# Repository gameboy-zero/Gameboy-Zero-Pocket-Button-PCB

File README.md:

&emsp;&emsp;&emsp;&emsp;&emsp;&emsp;&emsp;&emsp;&emsp;&emsp;&emsp;
# Informations
This button PCB is for the Gameboy Pocket to make a Gameboy Zero or an Arduboy.

## Pictures of the PCB

You find pictures in the images folder.

## Contributors:
DerNuntius

## Contact me
If you have any questions, improvements or updates about this project feel free to send me an e-mail. The e-mail address is pinned on my profile. 

Keep in mind that I'm not a native English speaker. If you can speak German you can send me an e-mail in German.

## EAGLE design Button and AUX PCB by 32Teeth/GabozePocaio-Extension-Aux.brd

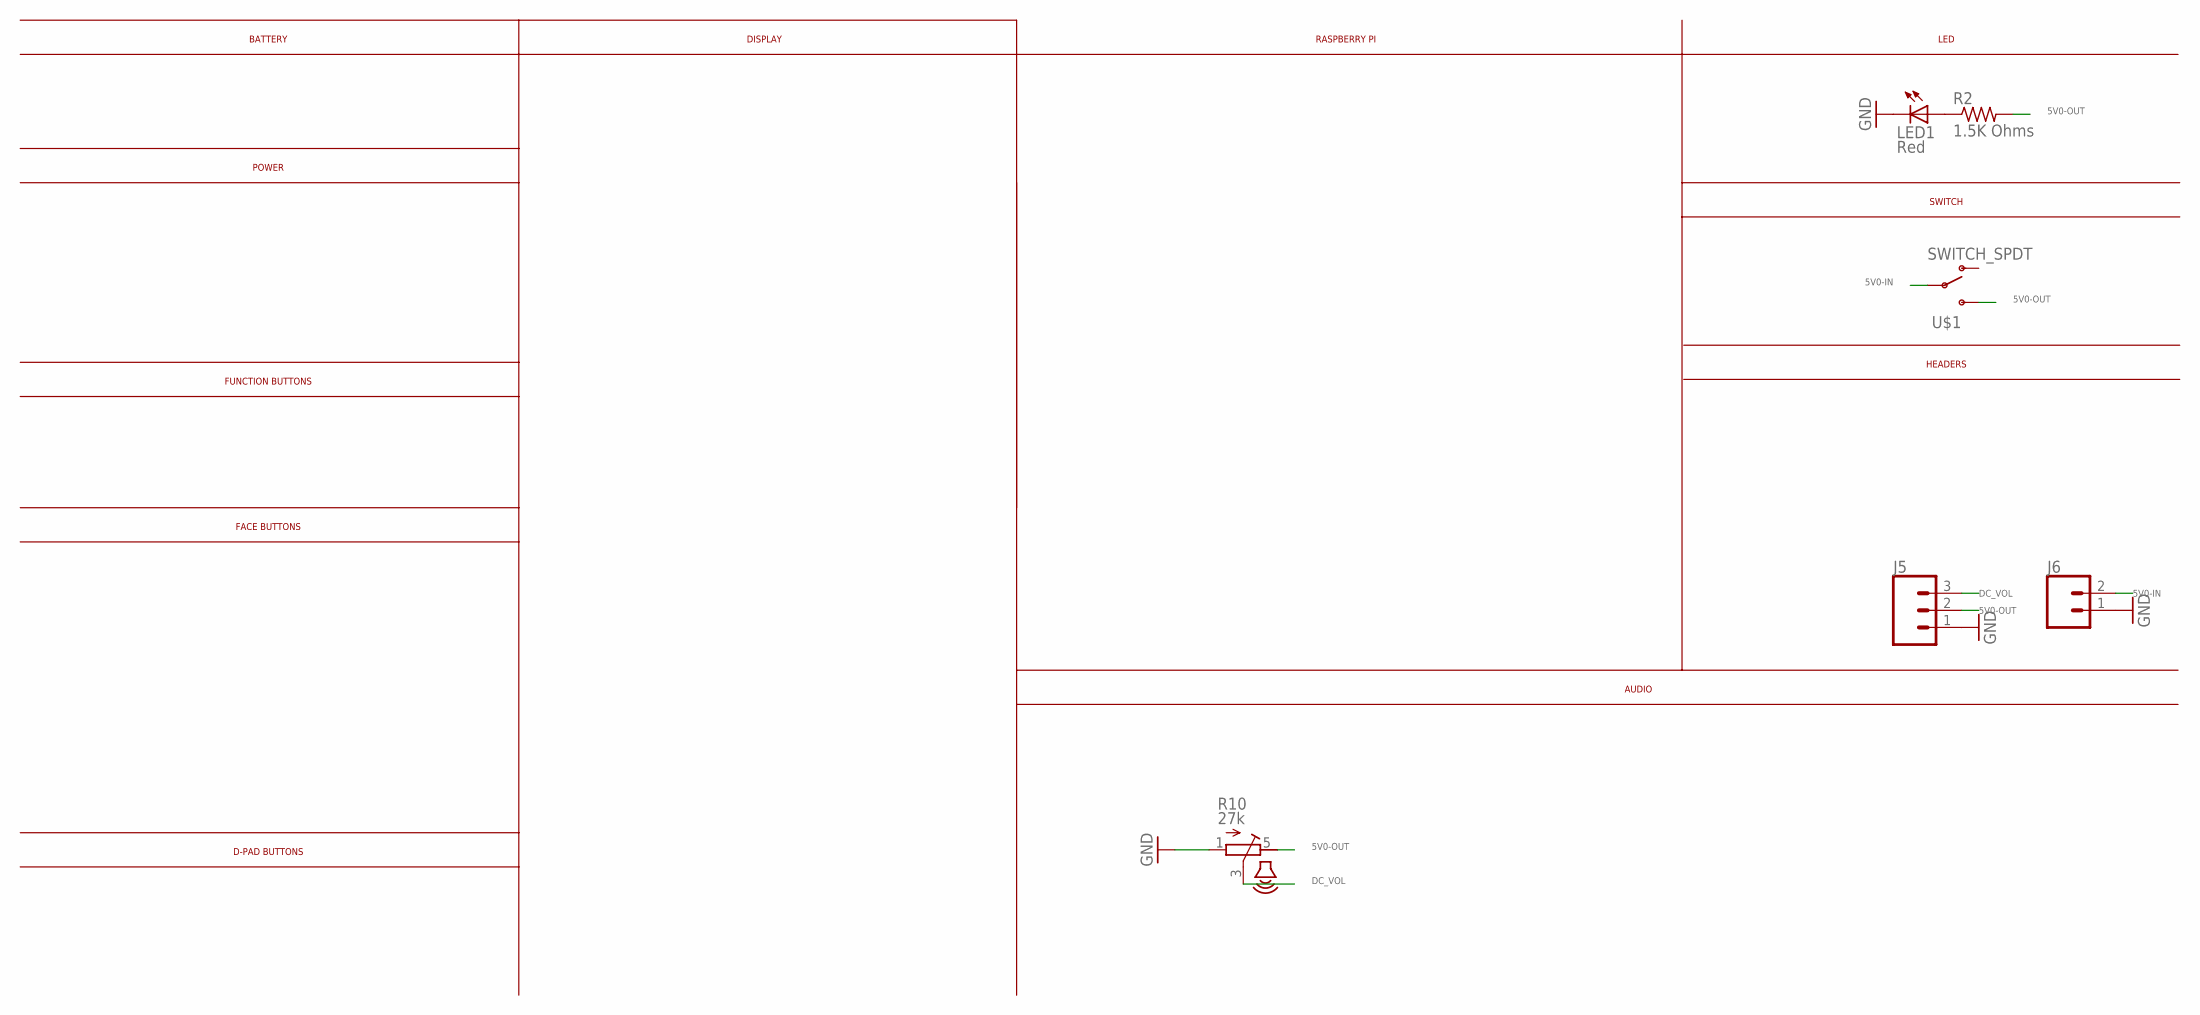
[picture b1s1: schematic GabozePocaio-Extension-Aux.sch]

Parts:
J5: CONN_031X03_NO_SILK; 1X03_NO_SILK
J6: CONN_021X02_NO_SILK; 1X02_NO_SILK
LED1: Red; LED3MM
R2: 1.5K Ohms; R0805
R10: 27k; VOLUME
U$1: SWITCH_SPDT; KPS-1290

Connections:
5V0-IN: J6.2, U$1.P
5V0-OUT: J5.2, R2.2, R10.5 (E), U$1.S
DC_VOL: J5.3, R10.3 (S)
GND: J5.1, J6.1, LED1.K (C), R10.1 (A)
LED: LED1.A, R2.1

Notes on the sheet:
D-PAD BUTTONS
FACE BUTTONS
FUNCTION BUTTONS
POWER
BATTERY
SWITCH
LED
DISPLAY
RASPBERRY PI
AUDIO
HEADERS

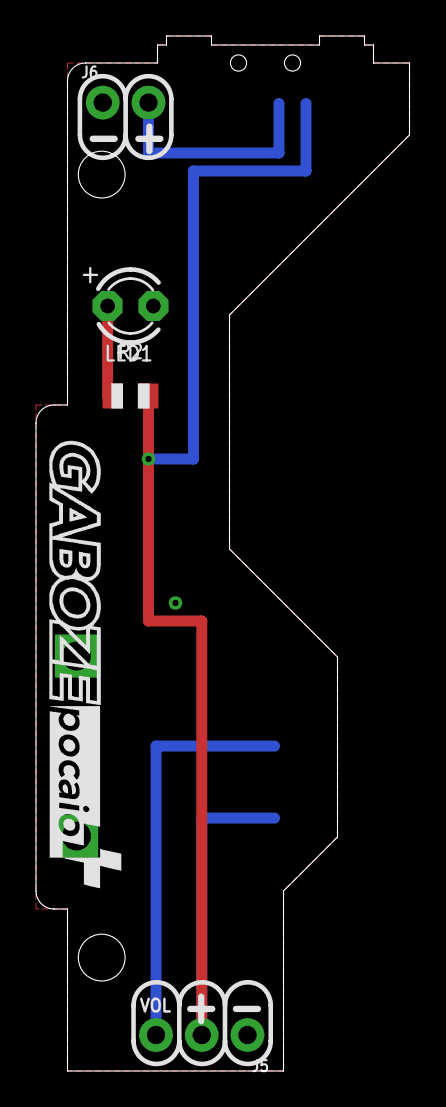
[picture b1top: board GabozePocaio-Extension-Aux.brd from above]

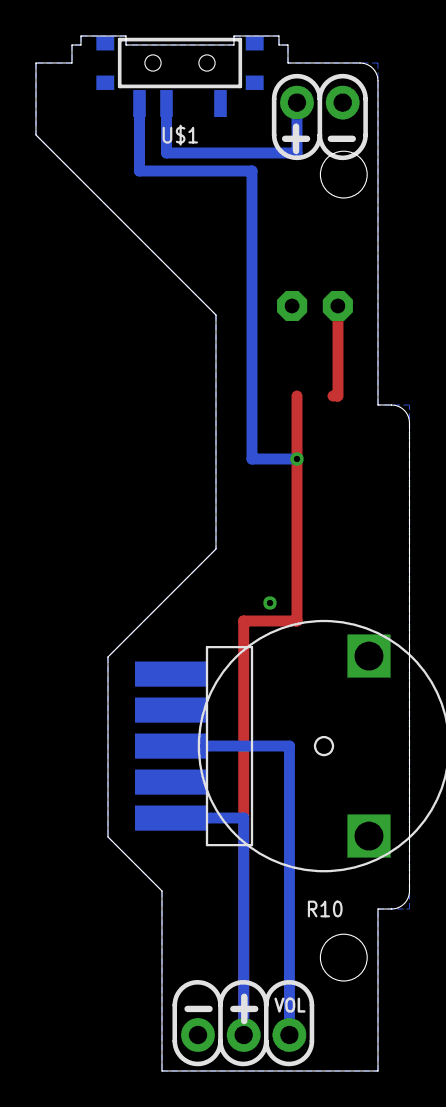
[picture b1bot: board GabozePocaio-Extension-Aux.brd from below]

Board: 2 copper layers, 20.7 x 57.5 mm, 6 parts (2 on the bottom side), 5 nets.

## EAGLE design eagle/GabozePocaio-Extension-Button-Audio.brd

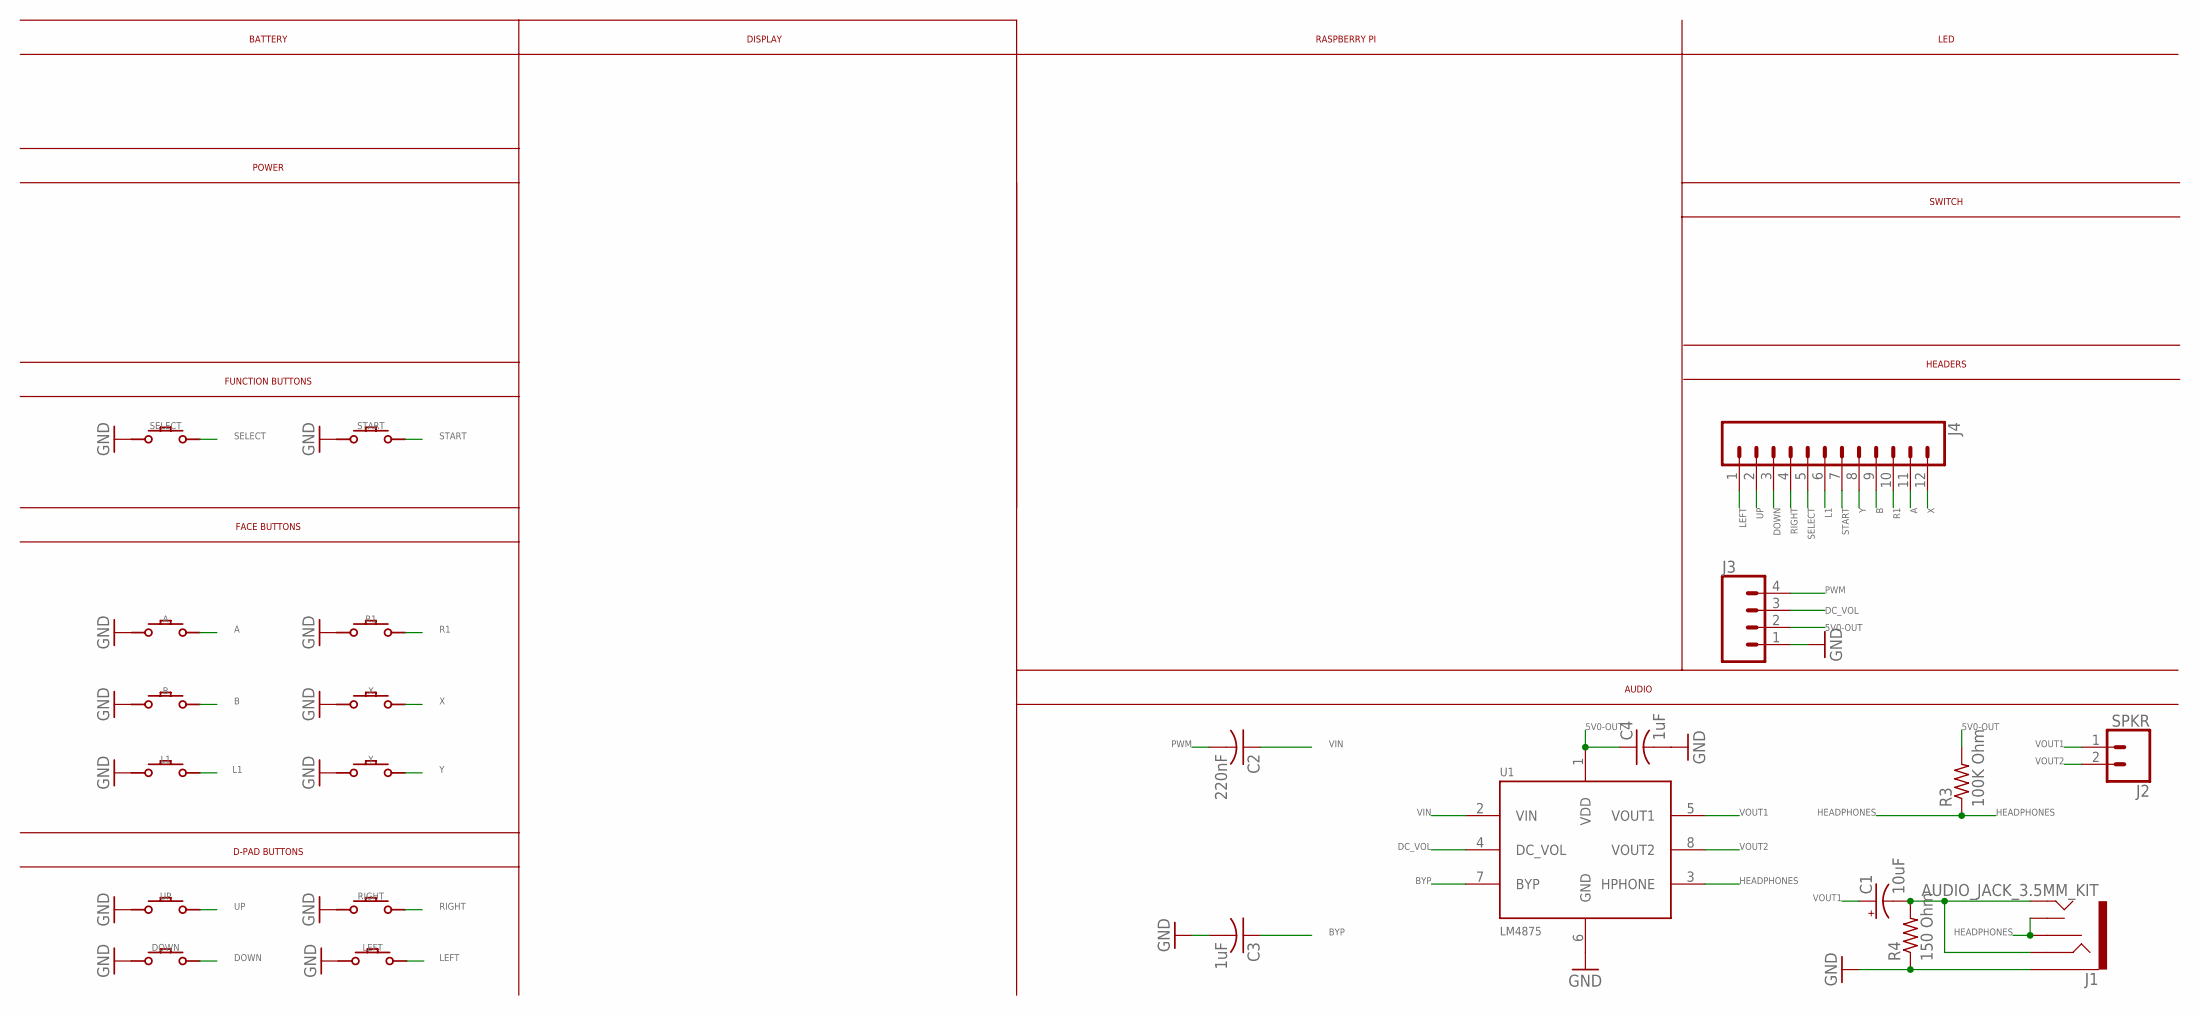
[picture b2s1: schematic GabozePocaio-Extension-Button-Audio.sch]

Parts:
A: CONDUCTIVE_BUTTON
B: CONDUCTIVE_BUTTON
C1: 10uF; EIA3216
C2: 220nF; C0805
C3, C4: 1uF; C0805
DOWN: CONDUCTIVE_BUTTON
J1: AUDIO_JACK_3.5MM_KIT; AUDIO-JACK-KIT
J2: SPKR; 1X02
J3: CONN_041X04_NO_SILK; 1X04_NO_SILK
J4: CONN_12NO_SILK; 1X12_NO_SILK
L1: CONDUCTIVE_BUTTON_DRILL
LEFT: CONDUCTIVE_BUTTON
R1: CONDUCTIVE_BUTTON_DRILL
R3: 100K Ohm; R0805
R4: 150 Ohm; R0805
RIGHT: CONDUCTIVE_BUTTON
SELECT: CONDUCTIVE_BUTTON_STARTSELECT
START: CONDUCTIVE_BUTTON_STARTSELECT
U1: LM4875; SOIC8
UP: CONDUCTIVE_BUTTON
X: CONDUCTIVE_BUTTON_DRILL
Y: CONDUCTIVE_BUTTON_DRILL

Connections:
5V0-OUT: C4.1, J3.2, R3.2, U1.1 (VDD)
A: A.P$ACTIVE, J4.11
B: B.P$ACTIVE, J4.9
BYP: C3.1, U1.7 (BYP)
DC_VOL: J3.3, U1.4 (DC_VOL)
DOWN: DOWN.P$ACTIVE, J4.3
GND: A.P$GND, B.P$GND, C3.2, C4.2, DOWN.P$GND, J1.SLEEVE, J3.1, L1.P$GND, LEFT.P$GND, R1.P$GND, R4.1, RIGHT.P$GND, SELECT.P$GND, START.P$GND, U1.6 (GND), UP.P$GND, X.P$GND, Y.P$GND
HEADPHONES: J1.RSH, J1.TSH, R3.1, U1.3 (HPHONE)
L1: J4.6, L1.P$ACTIVE
LEFT: J4.1, LEFT.P$ACTIVE
PWM: C2.2, J3.4
R1: J4.10, R1.P$ACTIVE
RIGHT: J4.4, RIGHT.P$ACTIVE
SELECT: J4.5, SELECT.P$ACTIVE
START: J4.7, START.P$ACTIVE
UP: J4.2, UP.P$ACTIVE
VIN: C2.1, U1.2 (VIN)
VIN1: C1.-, J1.RING, J1.TIP, R4.2
VOUT1: C1.+, J2.1, U1.5 (VOUT1)
VOUT2: J2.2, U1.8 (VOUT2)
X: J4.12, X.P$ACTIVE
Y: J4.8, Y.P$ACTIVE

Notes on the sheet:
D-PAD BUTTONS
FACE BUTTONS
FUNCTION BUTTONS
POWER
BATTERY
SWITCH
LED
DISPLAY
RASPBERRY PI
AUDIO
HEADERS

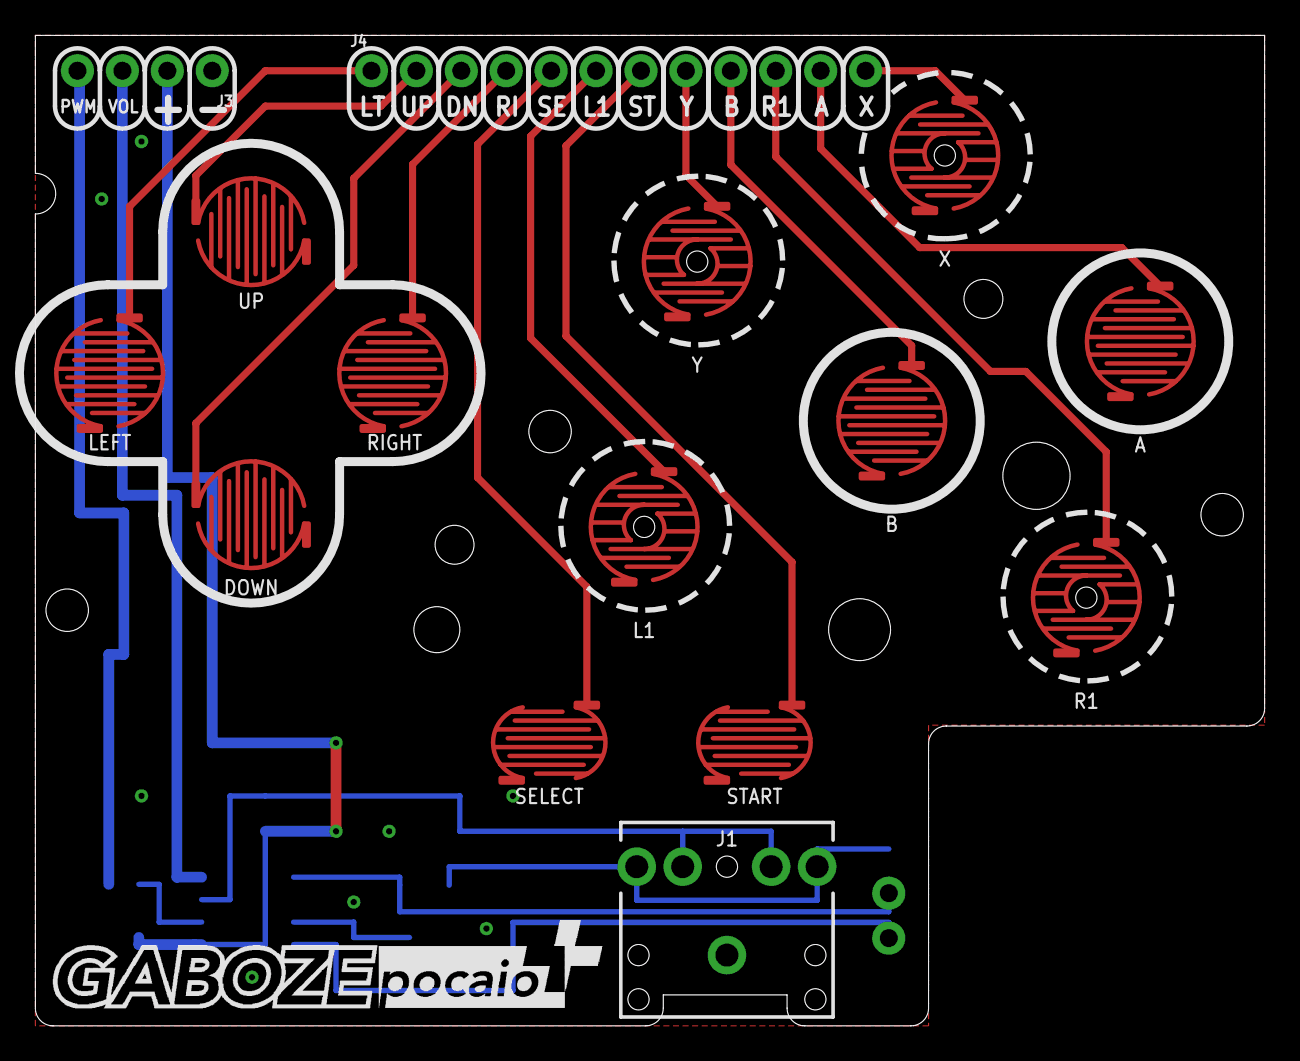
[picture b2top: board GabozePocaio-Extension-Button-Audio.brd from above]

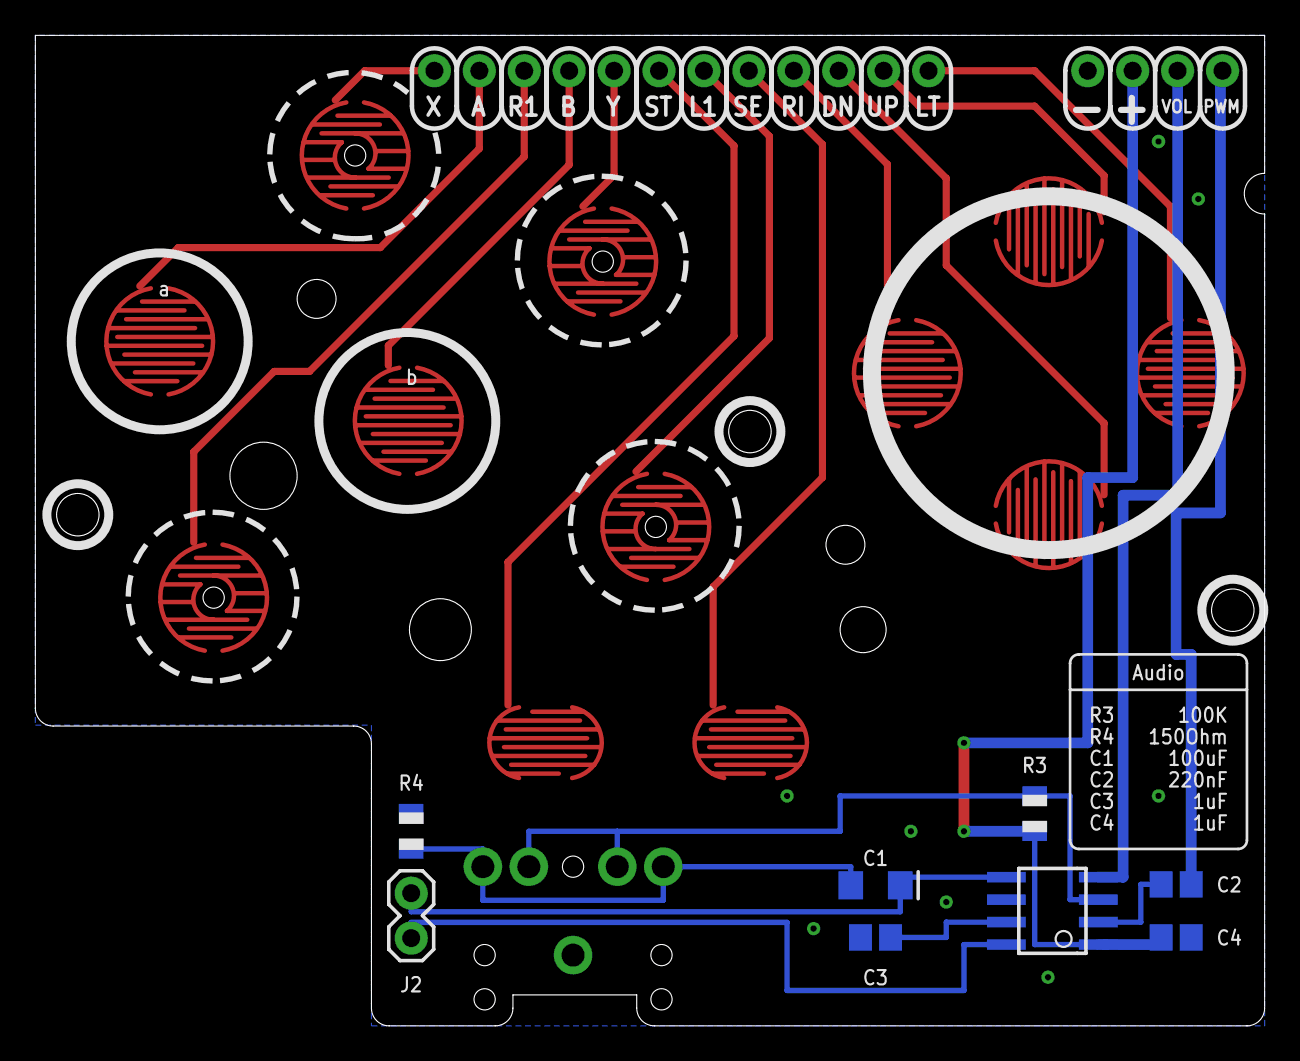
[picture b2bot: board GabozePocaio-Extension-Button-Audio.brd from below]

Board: 2 copper layers, 69.5 x 56.0 mm, 23 parts (8 on the bottom side), 22 nets.

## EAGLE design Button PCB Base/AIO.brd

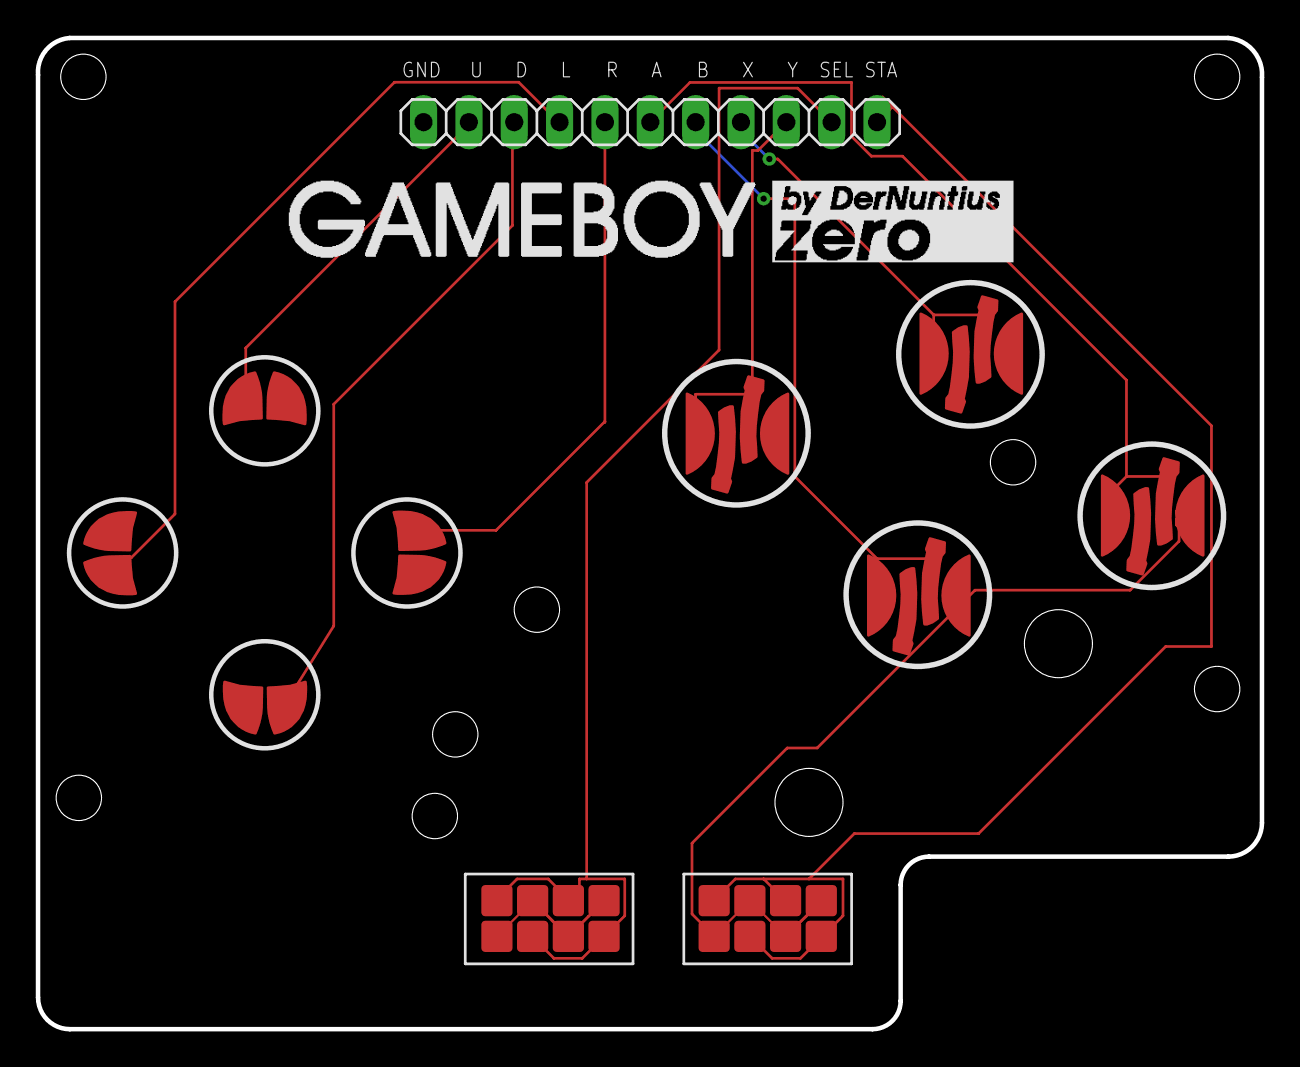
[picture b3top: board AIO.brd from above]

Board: 2 copper layers, 68.6 x 55.5 mm, 6 parts (0 on the bottom side), 11 nets.

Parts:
GND: 1X11
S1: D-PAD
S2: XY_BUTTON; AB_BUTTON
S3: AB_BUTTON
SELECT: CONDUCTIVE_BUTTON_STARTSELECTCONDUCTIVE_BUTTON_TH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; CONDUCTIVE_BUTTON_THICK_STARTSELECT
START: CONDUCTIVE_BUTTON_STARTSELECTCONDUCTIVE_BUTTON_TH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; CONDUCTIVE_BUTTON_THICK_STARTSELECT

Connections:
A: GND.6, S3.A@1, S3.A@2
B: GND.7, S3.B@1, S3.B@2
DOWN: GND.3, S1.LEFT
GND: GND.1, S1.GND@1, S1.GND@2, S1.GND@3, S1.GND@4, S2.GND@1, S2.GND@2, S2.GND@3, S2.GND@4, S3.GND@1, S3.GND@2, S3.GND@3, S3.GND@4, SELECT.P$ACTIVE, SELECT.P$ACTIVE1, SELECT.P$ACTIVE2, SELECT.P$ACTIVE3, START.P$ACTIVE, START.P$ACTIVE1, START.P$ACTIVE2, START.P$ACTIVE3
LEFT: GND.4, S1.UP
RIGHT: GND.5, S1.DOWN
SELECT: GND.10, SELECT.P$GND, SELECT.P$GND1, SELECT.P$GND2, SELECT.P$GND3
START: GND.11, START.P$GND, START.P$GND1, START.P$GND2, START.P$GND3
UP: GND.2, S1.RIGHT
X: GND.8, S2.A@1, S2.A@2
Y: GND.9, S2.B@1, S2.B@2

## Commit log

2019-01-25 Adding Eagle CAD files
2019-01-28 Second Revision
    - NEW Buttons
    - Smooth edges
    - NEW drill holes
2019-01-29 Tue 29 Jan 2019 05:59:02 EST - added eagle and gerber files back to master
2019-01-29 Second Revision
2019-01-29 Adding second PCB files by 32teeth
2019-03-02 Drill FIX
2019-03-02 Revision 2 Minor Fixes
2019-03-03 Revision V2
2019-03-03 Release V2

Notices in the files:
parts and their libraries:
SparkFun-Connectors: Licensing: Creative Commons ShareAlike 4.0 International - https://creativecommons.org/licenses/by-sa/4.0
